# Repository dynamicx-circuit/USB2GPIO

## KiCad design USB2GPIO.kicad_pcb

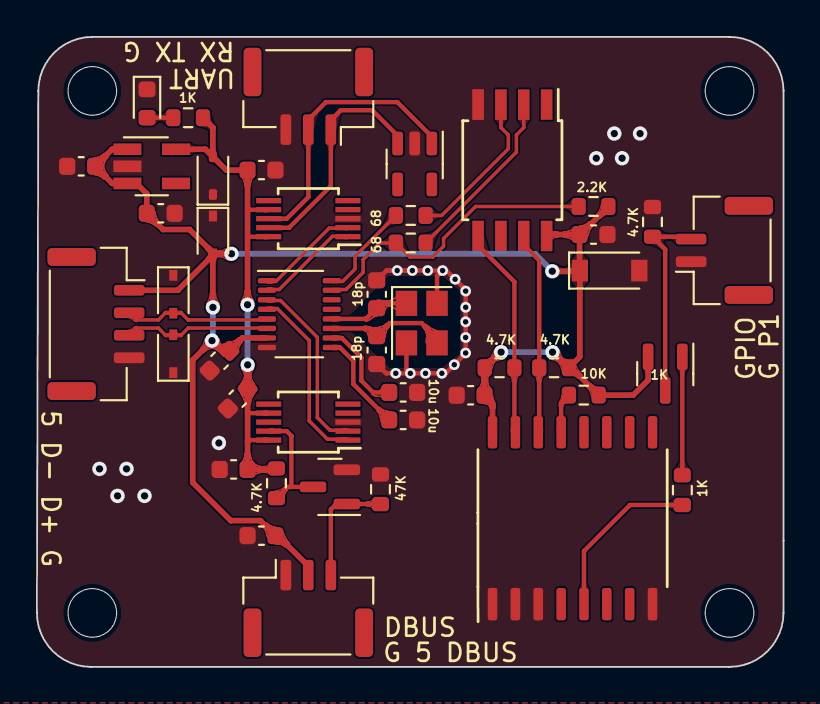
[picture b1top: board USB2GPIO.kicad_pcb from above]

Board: 2 copper layers, 41.5 x 35.0 mm, 48 parts (0 on the bottom side), 28 nets.

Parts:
C5, C7, C28, C29, C30, C31, C32, C33, C38: 100n; C_0603_1608Metric
C34, C35: 10u; C_0603_1608Metric
C36, C37: 18p; C_0603_1608Metric
D1, D10, D11, D12: BV05C; D_SOD-323
D9: LED; LED_0603_1608Metric
D13: 5V1; D_SOD-123
H1, H2, H3, H4: MountingHole; MountingHole_2.7mm_M2.5
J1: Conn_01x04; JST_GH_SM04B-GHS-TB_1x04-1MP_P1.25mm_Horizontal
J7, J8: Conn_01x03; JST_GH_SM03B-GHS-TB_1x03-1MP_P1.25mm_Horizontal
J9: Conn_01x02; JST_GH_SM02B-GHS-TB_1x02-1MP_P1.25mm_Horizontal
Q1: S8050; SOT-23
Q2: Q_PNP_BEC; SOT-23
R1, R14: 1K; R_0603_1608Metric
R2, R4, R16, R17: 4.7K; R_0603_1608Metric
R3: 47K; R_0603_1608Metric
R15: 10K; R_0603_1608Metric
R18: 2.2K; R_0603_1608Metric
R19, R20: 68; R_0603_1608Metric
U1: SOT-23-5
U2, U3: CH340E; MSOP-10_3x3mm_P0.5mm
U9: ATtiny85V-10S; SOIC-8W_5.3x5.3mm_P1.27mm
U10: PCF8574T; SOIC127P1032X265-16N
U11: HX9193; SOT-23-5_HandSoldering
U12: SL2.1S; SL2.1S-SSOP-16
Y2: 12M; Crystal_SMD_3225-4Pin_3.2x2.5mm

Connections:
+5V: C28.1, C29.1, C30.1, C31.1, C32.1, C38.1, D10.2 (A2), D13.1 (A1), J1.1, J7.2, Q2.2 (E), R15.2, R16.2, R17.2, R18.2, U9.8 (VCC), U10.16 (VDD), U11.1 (VIN), U11.3 (EN), U12.7 (VDD5)
/3V3: C5.1, C7.1, C33.1, D1.2 (A2), R2.1, R14.1, U2.7 (VCC), U2.10 (V3), U3.7 (VCC), U3.10 (V3), U11.5 (VOUT)
/DBUS/D+: U3.1 (UD+), U12.4 (DP1)
/DBUS/D-: U3.2 (UD-), U12.3 (DM1)
/DBUS/DBus: J7.3, Q1.1 (B), R3.1
/GPIO/*D+: R20.1, U9.3 (XTAL2/PB4)
/GPIO/*D-: R19.1, U9.2 (XTAL1/PB3)
/GPIO/D+: R20.2, U12.16 (DP3)
/GPIO/D-: R18.1, R19.2, U12.15 (DM3)
/GPIO/P1: J9.2, Q2.3 (C), R4.2
/GPIO/SCL: R17.1, U9.7 (PB2), U10.14 (SCL)
/GPIO/SDA: R16.1, U9.5 (AREF/PB0), U10.15 (SDA)
/UART/D+: U2.1 (UD+), U12.2 (DP2)
/UART/D-: U2.2 (UD-), U12.1 (DM2)
/UART/RXD: J8.1, U1.3 (I/O2), U2.9 (RXD)
/UART/TXD: J8.2, U1.1 (I/O1), U2.8 (TXD)
/USB_HUB/D+: D12.2 (A2), J1.3, U12.6 (UDP)
/USB_HUB/D-: D11.2 (A2), J1.2, U12.5 (UDM)
/USB_HUB/XIN: C37.1, U12.12 (XIN), Y2.1
/USB_HUB/XOUT: C36.1, U12.11 (XOUT), Y2.3
GND: C5.2, C7.2, C28.2, C29.2, C30.2, C31.2, C32.2, C33.2, C34.2, C35.2, C36.2, C37.2, C38.2, D1.1 (A1), D9.1 (K), D10.1 (A1), D11.1 (A1), D12.1 (A1), D13.2 (A2), J1.4, J7.1, J8.3, J9.1, Q1.2 (E), R3.2, R4.1, U1.2 (GND), U2.3 (GND), U3.3 (GND), U9.4 (GND), U10.1 (A0), U10.2 (A1), U10.3 (A2), U10.8 (VSS), U11.2 (GND), U12.8 (VSS), Y2.2, Y2.4
unnamed: D9.2 (A), R14.2
unnamed: Q1.3 (C), R2.2, U3.9 (RXD)
unnamed: Q2.1 (B), R1.1
unnamed: R1.2, U10.5 (P1)
unnamed: R15.1, U10.13 (~INT)
unnamed: C35.1, U12.10 (VDD18)
unnamed: C34.1, U12.9 (VDD33)

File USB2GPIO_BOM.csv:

"Comment","Description","Designator","Footprint","LibRef","Pins","Quantity","PartNumber","url",
"100n","desc","C5,C7,C28,C29,C30,C31,C32,C33,C38,","C_0603_1608Metric","libref","2","9","","",
"10u","desc","C34,C35,","C_0603_1608Metric","libref","2","2","","",
"18p","desc","C36,C37,","C_0603_1608Metric","libref","2","2","","",
"LED","desc","D9,","LED_0603_1608Metric","libref","2","1","","",
"BV05C","desc","D10,D11,D12,","D_SOD-323","libref","2","3","","",
"5V1","desc","D13,","D_SOD-123","libref","2","1","","",
"Conn_01x04","desc","J1,","JST_GH_SM04B-GHS-TB_1x04-1MP_P1.25mm_Horizontal","libref","6","1","","",
"Conn_01x03","desc","J7,J8,","JST_GH_SM03B-GHS-TB_1x03-1MP_P1.25mm_Horizontal","libref","5","2","","",
"Conn_01x02","desc","J9,","JST_GH_SM02B-GHS-TB_1x02-1MP_P1.25mm_Horizontal","libref","4","1","","",
"S8050","desc","Q1,","SOT-23","libref","3","1","","",
"4.7K","desc","R2,R16,R17,","R_0603_1608Metric","libref","2","3","","",
"47K","desc","R3,","R_0603_1608Metric","libref","2","1","","",
"1K","desc","R14,R30,","R_0603_1608Metric","libref","2","2","","",
"10K","desc","R15,","R_0603_1608Metric","libref","2","1","","",
"2.2K","desc","R18,","R_0603_1608Metric","libref","2","1","","",
"68","desc","R19,R20,","R_0603_1608Metric","libref","2","2","","",
"CH340E","desc","U2,U3,","MSOP-10_3x3mm_P0.5mm","libref","10","2","","",
"ATtiny85V-10S","desc","U9,","SOIC-8W_5.3x5.3mm_P1.27mm","libref","8","1","","",
"PCF8574T","desc","U10,","SOIC127P1032X265-16N","libref","16","1","","",
"HX9193","desc","U11,","SOT-23-5_HandSoldering","libref","5","1","","",
"SL2.1S","desc","U12,","SL2.1S-SSOP-16","libref","16","1","","",
"12M","desc","Y2,","Crystal_SMD_3225-4Pin_3.2x2.5mm","libref","4","1","","",
"Through Hole Items ",
"MountingHole","desc","H1,H2,H3,H4,","MountingHole_2.7mm_M2.5","libref","1","4","","",

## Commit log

2022-08-29 Add USB2GPIO sch
2022-09-01 PCB drawn
2022-09-02 Change footprint of MX1.25 and change some routings and silkscreens
2022-11-15 Change '5V' tag to '+5V' net
2022-11-15 Change gpio-pin from P0 to P1
2022-12-12 Change the map and rebuild the PCB
2023-01-12 Add output protect
2023-03-05 A try to add pull-up resistor for gpio_out
2023-04-15 Change pnp to a pull-up resistance
2023-04-30 Add ESD protection
2023-05-20 Return to PNP-out
